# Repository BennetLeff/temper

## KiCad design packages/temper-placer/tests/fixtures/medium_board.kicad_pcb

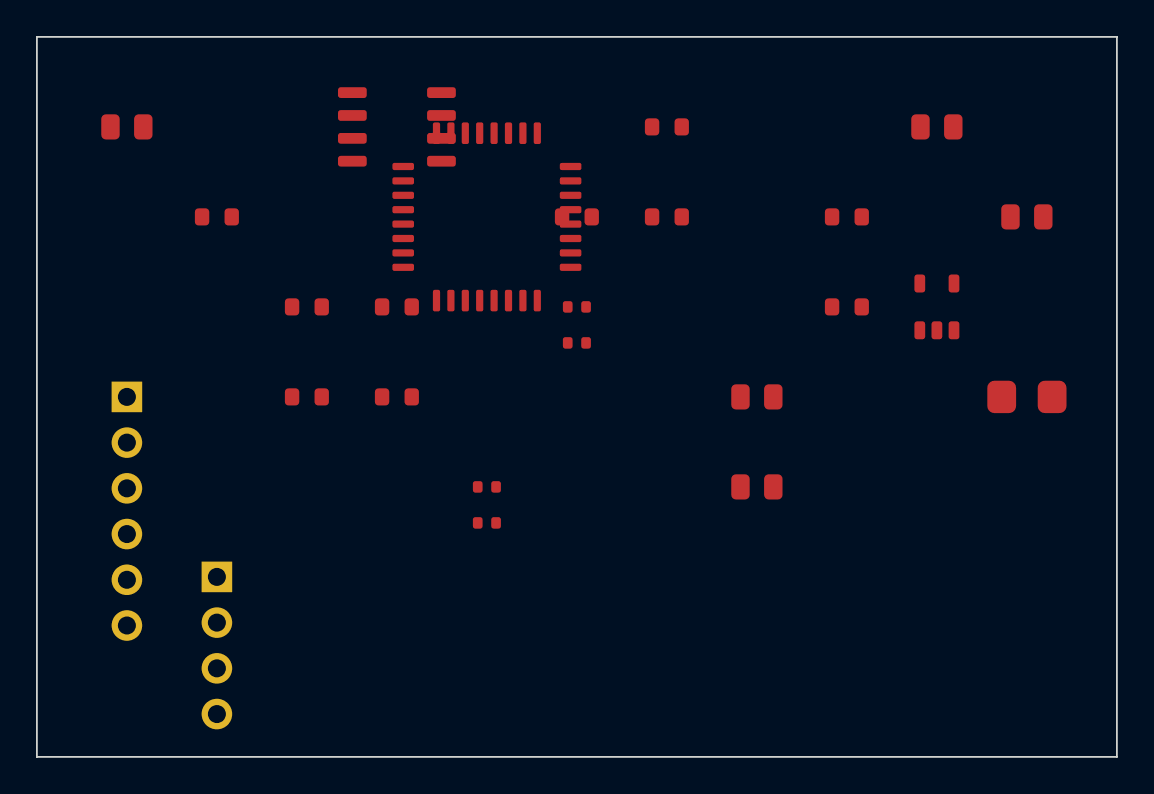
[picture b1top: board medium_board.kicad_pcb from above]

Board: 2 copper layers, 60.0 x 40.0 mm, 25 parts (0 on the bottom side), 18 nets, no tracks yet.

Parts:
C1, C2: 100nF; C_0603_1608Metric
C3: 10nF; C_0603_1608Metric
C4: 1uF; C_0603_1608Metric
C5, C6: 10uF; C_0805_2012Metric
C7, C8: 100pF; C_0402_1005Metric
J1: PROG; PinHeader_1x06_P2.54mm_Vertical
J2: I2C; PinHeader_1x04_P2.54mm_Vertical
L1: 10uH; L_0805_2012Metric
L2: 4.7uH; L_1206_3216Metric
R1, R2: 10k; R_0603_1608Metric
R3, R4: 4.7k; R_0603_1608Metric
R5, R6: 1k; R_0603_1608Metric
R7, R8: 100; R_0805_2012Metric
R9, R10: 100k; R_0402_1005Metric
U1: LM358; SOIC-8_3.9x4.9mm_P1.27mm
U2: AMS1117-3.3; SOT-23-5
U3: ATmega328P; TQFP-32_7x7mm_P0.8mm

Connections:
GND: C1.2, C2.2, C3.2, C4.2, C5.2, C6.2, C7.2, C8.2, J1.2, J2.2, R8.2, U1.4, U2.2, U2.3, U3.6, U3.16, U3.22, U3.27, U3.32
I2C_SCL: J2.4, R2.2, U3.10
I2C_SDA: J2.3, R1.2, U3.9
PWM1: R5.1, U3.17
PWM2: R6.1, U3.18
SIG_A: R1.1, R9.2, U1.1, U3.11, U3.19, U3.28
SIG_B: R2.1, R10.2, U1.2, U3.12, U3.20, U3.29
SIG_C: R5.2, U1.3, U3.13, U3.23, U3.30
SIG_D: R6.2, U1.5, U1.6, U3.14, U3.24, U3.31
SPI_CLK: C7.1, J1.5, U3.3
SPI_CS: C8.1, J1.6, U3.4
SPI_MISO: J1.4, R4.1, U3.2
SPI_MOSI: J1.3, R3.1, U3.1
UART_RX: R10.1, U3.8
UART_TX: R9.1, U3.7
VBAT: C3.1, L1.2, R7.2, U3.25
VCC: C1.1, C4.1, C5.1, L1.1, L2.2, R7.1, U1.7, U1.8, U2.1, U3.26
VCC_3V3: C2.1, C6.1, J1.1, J2.1, L2.1, R3.2, R4.2, R8.1, U2.4, U2.5, U3.5, U3.15, U3.21

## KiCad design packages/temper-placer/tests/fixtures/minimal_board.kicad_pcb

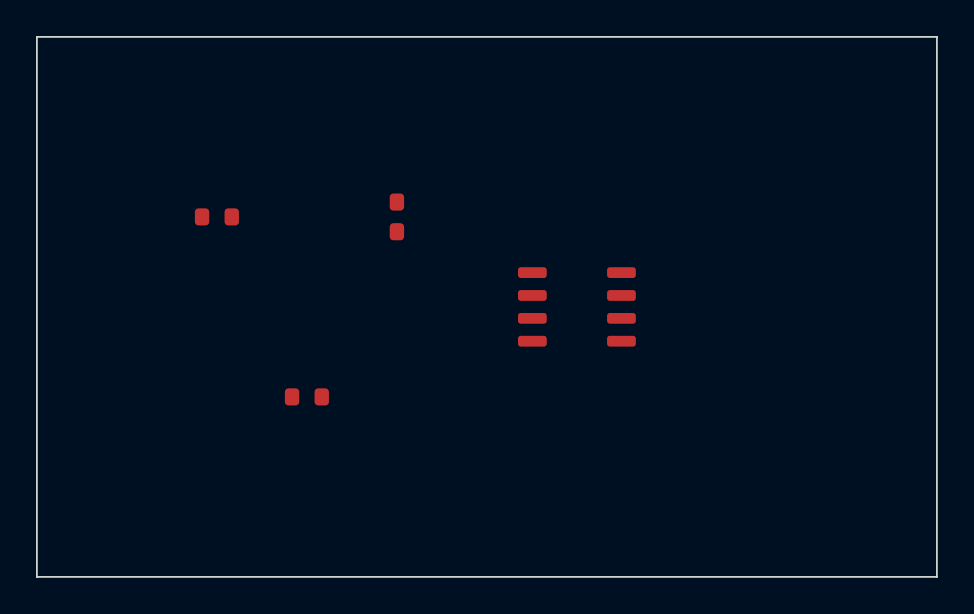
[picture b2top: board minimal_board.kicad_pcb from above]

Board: 2 copper layers, 50.0 x 30.0 mm, 4 parts (0 on the bottom side), 4 nets, no tracks yet.

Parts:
C1: 100nF; C_0603_1608Metric
R1: 10k; R_0603_1608Metric
R2: 4.7k; R_0603_1608Metric
U1: LM358; SOIC-8_3.9x4.9mm_P1.27mm

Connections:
GND: C1.2, R2.1, U1.4
SIG1: R1.1, U1.1, U1.5
SIG2: R1.2, R2.2, U1.2, U1.3, U1.6
VCC: C1.1, U1.7, U1.8

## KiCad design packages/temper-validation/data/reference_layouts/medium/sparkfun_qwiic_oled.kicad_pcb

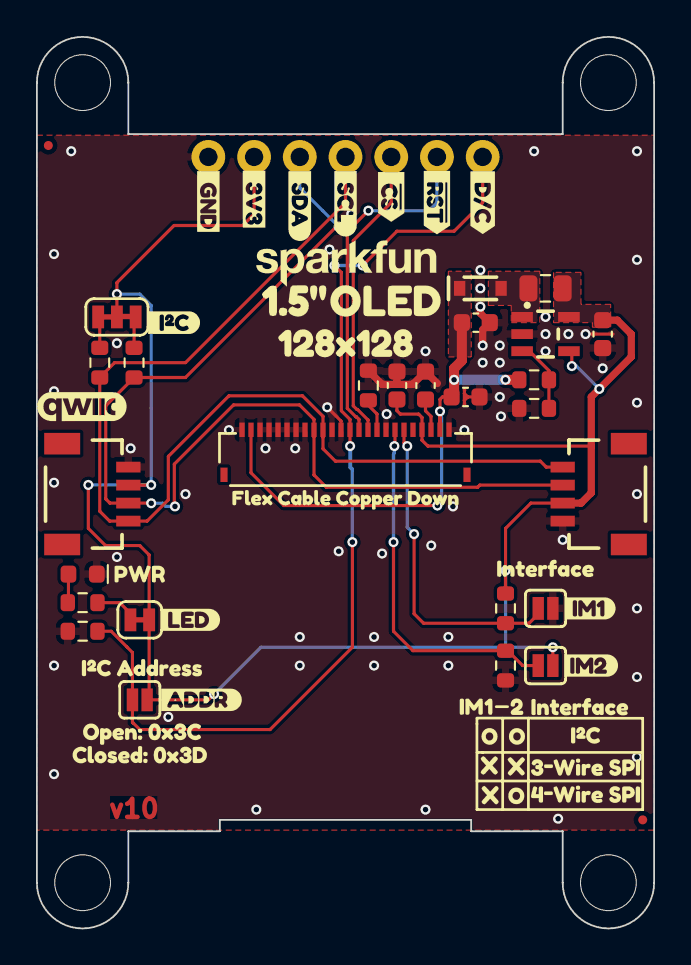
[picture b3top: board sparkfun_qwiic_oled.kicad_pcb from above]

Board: 2 copper layers, 34.3 x 49.5 mm, 70 parts (1 on the bottom side), 18 nets.

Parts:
C1, C2: 1.0uF; C_0603_1608Metric
C3, C4, C5: 4.7uF; C_0603_1608Metric
D1: Red; LED_0603_1608Metric_Red
D2: PMEG4005EJ; SOD-323
FID3, FID4: Fiducial_0.5mm; Fiducial_0.5mm_Mask1mm
G4: OSHW_Logo; Creative_Commons_License
J1, J2: Qwiic_RA; JST_SMD_1.0mm-4_Black
J4: Conn_01x24_FPC; FPC_0.5mm-24
J5: Conn_01x07; 1x07
JP1: LED; Jumper_2_NC_Trace
JP2: I2C; Jumper_3_NC-2_Trace
JP3: ADR; Jumper_2_NO
JP6: IM1; Jumper_2_NO
JP7: IM2; Jumper_2_NO
L1: 10uH; C_0805_2012Metric
R1: 18k; R_0603_1608Metric
R2: 2.1k; R_0603_1608Metric
R3: 4.7k; R_0603_1608Metric
R4, R5: 2.2k; R_0603_1608Metric
R6: 549k; R_0603_1608Metric
R7, R10, R11: 10k; R_0603_1608Metric
ST1, ST2, ST3, ST4: Standoff
TP1: 1.0mm; TestPoint-1.0mm
U2: WEO128128ASAP3N00000; OLED_1.5in_128x128-Folded
U5: AP3012; SOT23-5
kibuzzard-65A8A8B4: G***; kibuzzard-65A8A8B4
kibuzzard-67BF7EBF: G***; kibuzzard-67BF7EBF
kibuzzard-67BF7ED9: G***; kibuzzard-67BF7ED9
kibuzzard-67BF7F2F: G***; kibuzzard-67BF7F2F
kibuzzard-67BF7F13: G***; kibuzzard-67BF7F13
kibuzzard-680E7A4B: G***; kibuzzard-680E7A4B
kibuzzard-680E7A69: G***; kibuzzard-680E7A69
kibuzzard-680FC73E: G***; kibuzzard-680FC73E
kibuzzard-680FC89E: G***; kibuzzard-680FC89E
kibuzzard-680FC883: G***; kibuzzard-680FC883
kibuzzard-680FC897: G***; kibuzzard-680FC897
kibuzzard-680FC957: G***; kibuzzard-680FC957
kibuzzard-680FCA9D: G***; kibuzzard-680FCA9D
kibuzzard-680FCA96: G***; kibuzzard-680FCA96
kibuzzard-680FCADD: G***; kibuzzard-680FCADD
kibuzzard-680FCAEB: G***; kibuzzard-680FCAEB
kibuzzard-684C656A: G***; kibuzzard-684C656A
kibuzzard-685B1775: G***; kibuzzard-685B1775
kibuzzard-6893A61C, kibuzzard-6893A61C#2, kibuzzard-6893A61C#3: G***; kibuzzard-6893A61C
kibuzzard-689381EF, kibuzzard-689381EF#2, kibuzzard-689381EF#3: G***; kibuzzard-689381EF
kibuzzard-6851867B: G***; kibuzzard-6851867B
kibuzzard-6851871B: G***; kibuzzard-6851871B
kibuzzard-6893822D: G***; kibuzzard-6893822D
kibuzzard-6893824B: G***; kibuzzard-6893824B
kibuzzard-68518672: G***; kibuzzard-68518672
kibuzzard-68938236: G***; kibuzzard-68938236
kibuzzard-68938244: G***; kibuzzard-68938244
kibuzzard-68938257: G***; kibuzzard-68938257
kibuzzard-68938266: G***; kibuzzard-68938266
kibuzzard-68938270: G***; kibuzzard-68938270

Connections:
3.3V: C1.1, C4.1, J1.2, J2.2, J4.21, J5.2, JP1.2 (B), JP2.2 (B), JP3.2 (B), JP7.2 (B), L1.1, R10.1, U5.4 (~SHDN), U5.5 (IN)
12V: C2.1, C5.1, D2.1 (K), J4.2, J4.23, R1.2, TP1.1
/12V_OUT: D2.2 (A), L1.2, U5.1 (SW)
D/C: J4.13, J5.7, JP3.1 (A), R7.2
GND: C1.2, C2.2, C3.2, C4.2, C5.2, D1.1 (K), J1.1, J2.1, J4.1, J4.3, J4.4, J4.5, J4.6, J4.7, J4.8, J4.11, J4.12, J4.17, J4.24, J5.1, JP6.1 (A), R2.1, R6.1, R7.1, R11.2, U5.2 (GND)
unnamed: D1.2 (A), R3.1
unnamed: J4.16, R6.2
unnamed: J4.18, JP7.1 (A), R11.1
unnamed: J4.19, JP6.2 (B), R10.2
unnamed: C3.1, J4.22
unnamed: JP1.1 (A), R3.2
unnamed: JP2.1 (A), R5.1
unnamed: JP2.3 (C), R4.2
unnamed: R1.1, R2.2, U5.3 (FB)
SCL/SCK: J1.4, J2.4, J4.10, J5.4, R5.2
SDA/SDI: J1.3, J2.3, J4.9, J5.3, R4.1
~CS: J4.15, J5.5
~RST: J4.14, J5.6

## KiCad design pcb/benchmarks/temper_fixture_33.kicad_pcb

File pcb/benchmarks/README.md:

# Benchmark Fixtures (quarantined)

Boards in this directory are **synthetic benchmark fixtures**, not the
production design. They exist only to exercise the placer/router algorithms.

## Rules

- A board here can **never** be a production pipeline input. The artifact
  identity gate (plan `docs/plans/2026-07-15-001-feat-artifact-identity-provenance-plan.md`,
  unit U3/U4) infers role from this path: `pcb/benchmarks/**` ⇒ fixture.
- Nothing here is derived from `elec/src/*.ato`. Do not treat it as the design.

## Current contents

- `temper_fixture_33.kicad_pcb` — 33-component synthetic fixture. The real
  Temper design has ~100 components (`elec/build/default.net`).

## Sunset

This directory is temporary. Once the production board is generated from
schematics and the placer/router are re-benchmarked against it (plan
`2026-07-15-001` unit U6), this fixture is deleted and the committed
`.kicad_pcb` inventory becomes exactly one board.

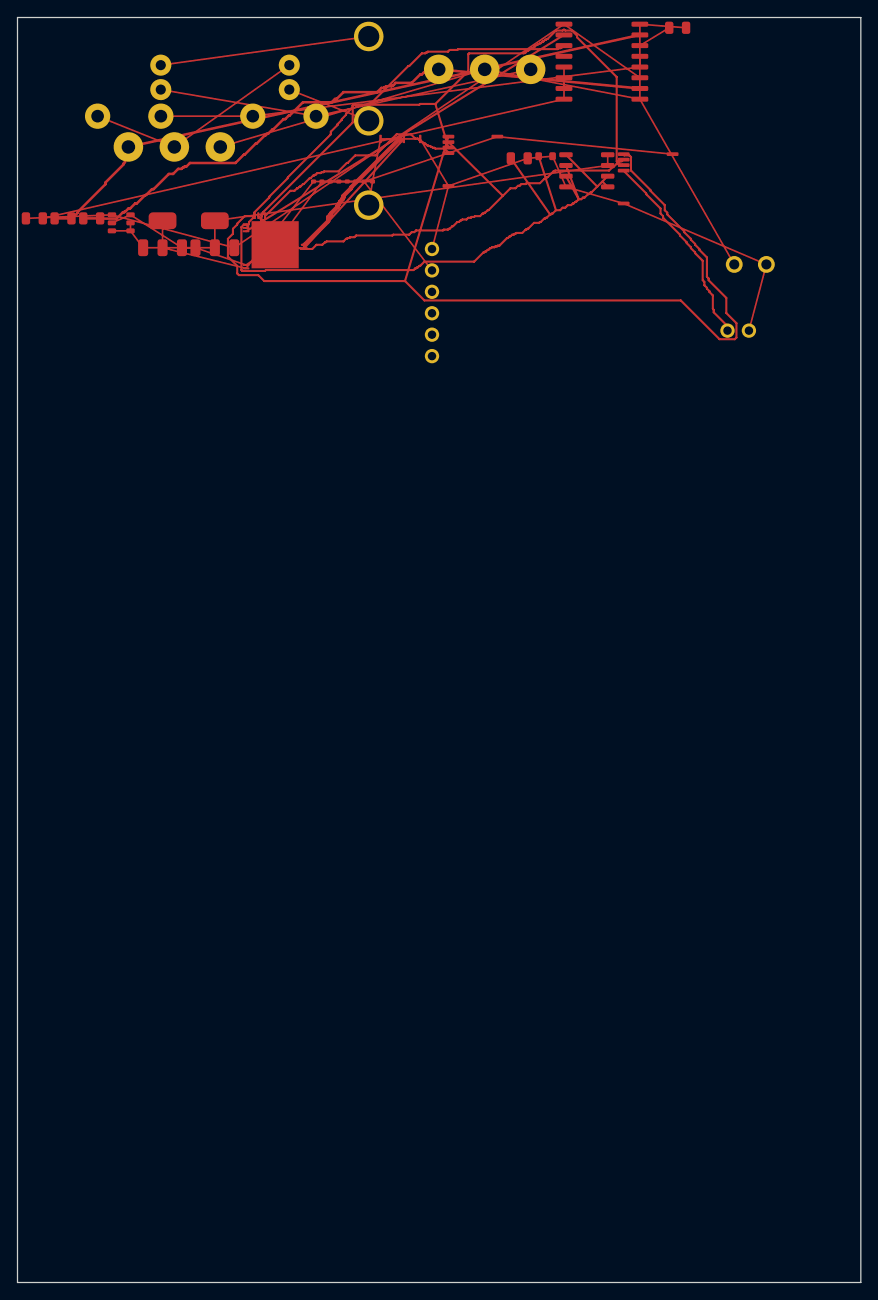
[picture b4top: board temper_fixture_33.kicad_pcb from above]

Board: 4 copper layers, 100.0 x 150.0 mm, 33 parts (0 on the bottom side), 24 nets.

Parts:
C_BOOT: 10uF; C_0805_2012Metric
C_BUS1, C_BUS2: 330uF/400V; CP_Radial_D18.0mm_P7.50mm
C_CT_FILT: 100pF; C_0603_1608Metric
C_MCU_1, C_MCU_2, C_MCU_3: 100nF; C_0402_1005Metric
C_MCU_4: 10uF; C_0402_1005Metric
C_VCC: 10uF; C_0805_2012Metric
D1, D2: 1N5408; D_DO-201AD_P15.24mm_Horizontal
J_AC_IN: IEC_C14; IEC_C14_Male
J_COIL: Coil; PhoenixContact_MCV_1,5_2-G-3.81_1x02_P3.81mm_Vertical
J_DEBUG: Debug; PinHeader_1x06_P2.54mm_Vertical
J_NTC: NTC; PinHeader_1x02_P2.54mm_Vertical
J_USB: USB_C; USB_C_Receptacle_HRO_TYPE-C-31-M-12
MAX31865: MAX31865; TSSOP-20_4.4x6.5mm_P0.65mm
MH1, MH2, MH3, MH4: MountingHole_3.2mm_M3
Q1, Q2: IKW40N120H3; TO-247-3_Horizontal_TabDown
R_BURDEN: 33R; R_0805_2012Metric
R_GATE_H: 4.7R; R_0805_2012Metric
R_GATE_L: 4.7R; R_0805_2012Metric
U_BUCK: LMR51430; SOT-23-6
U_CT: MAX31865; TSSOP-20_4.4x6.5mm_P0.65mm
U_GATE: UCC21550; SOIC-16W_7.5x10.3mm_P1.27mm
U_LDO_3V3: AMS1117-3.3; SOT-223-3_TabPin2
U_LDO_5V: AMS1117-5.0; SOT-223-3_TabPin2
U_MCU: ESP32-S3-WROOM-1; QFN-56-1EP_7x7mm_P0.4mm_EP5.6x5.6mm
U_OPAMP_CT: LM358; SOIC-8_3.9x4.9mm_P1.27mm

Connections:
+3V3: C_MCU_1.1, C_MCU_2.1, C_MCU_3.1, C_MCU_4.1, J_DEBUG.2, MAX31865.20, U_CT.20, U_LDO_3V3.2, U_LDO_3V3.4, U_MCU.1
+5V: U_BUCK.2, U_BUCK.4, U_LDO_3V3.3, U_LDO_5V.2, U_LDO_5V.4, U_OPAMP_CT.7, U_OPAMP_CT.8
+15V: C_VCC.1, U_BUCK.3, U_GATE.1, U_GATE.11, U_LDO_5V.3
AC_L: D1.1, J_AC_IN.1
AC_N: D2.2, J_AC_IN.2
CGND: C_VCC.2, U_GATE.5, U_GATE.6, U_GATE.7, U_GATE.8
DC_BUS+: C_BUS1.1, D1.2, Q1.2
DC_BUS-: C_BUS2.2, D2.1, Q2.3
GATE_H: Q1.1, R_GATE_H.1, R_GATE_H.2, U_GATE.15
GATE_L: Q2.1, R_GATE_L.1, R_GATE_L.2, U_GATE.10
GND: C_CT_FILT.2, C_MCU_1.2, C_MCU_2.2, C_MCU_3.2, C_MCU_4.2, J_AC_IN.3, J_COIL.2, J_DEBUG.1, J_NTC.2, J_USB.A1, J_USB.A12, MAX31865.10, R_BURDEN.2, U_BUCK.1, U_BUCK.5, U_BUCK.6, U_CT.10, U_LDO_3V3.1, U_LDO_5V.1, U_MCU.2, U_MCU.57, U_OPAMP_CT.4
I_SENSE: C_CT_FILT.1, R_BURDEN.1, U_MCU.15, U_OPAMP_CT.1, U_OPAMP_CT.2, U_OPAMP_CT.3, U_OPAMP_CT.5, U_OPAMP_CT.6
PGND: C_BUS1.2, C_BUS2.1, U_GATE.12, U_GATE.13
PWM_H: U_GATE.2, U_MCU.13
PWM_L: U_GATE.3, U_MCU.14
SPI_CLK: MAX31865.1, U_CT.1, U_MCU.20
SPI_CS_TEMP: U_CT.4, U_MCU.23
SPI_MISO: MAX31865.3, U_CT.3, U_MCU.22
SPI_MOSI: MAX31865.2, U_CT.2, U_MCU.21
SW_NODE: C_BOOT.2, J_COIL.1, Q1.3, Q2.2, U_GATE.9, U_GATE.16
TEMP_SENSE: J_NTC.1, MAX31865.4
USB_D+: J_USB.A6, U_MCU.40
USB_D-: J_USB.B6, U_MCU.41
VCC_BOOT: C_BOOT.1, U_GATE.14

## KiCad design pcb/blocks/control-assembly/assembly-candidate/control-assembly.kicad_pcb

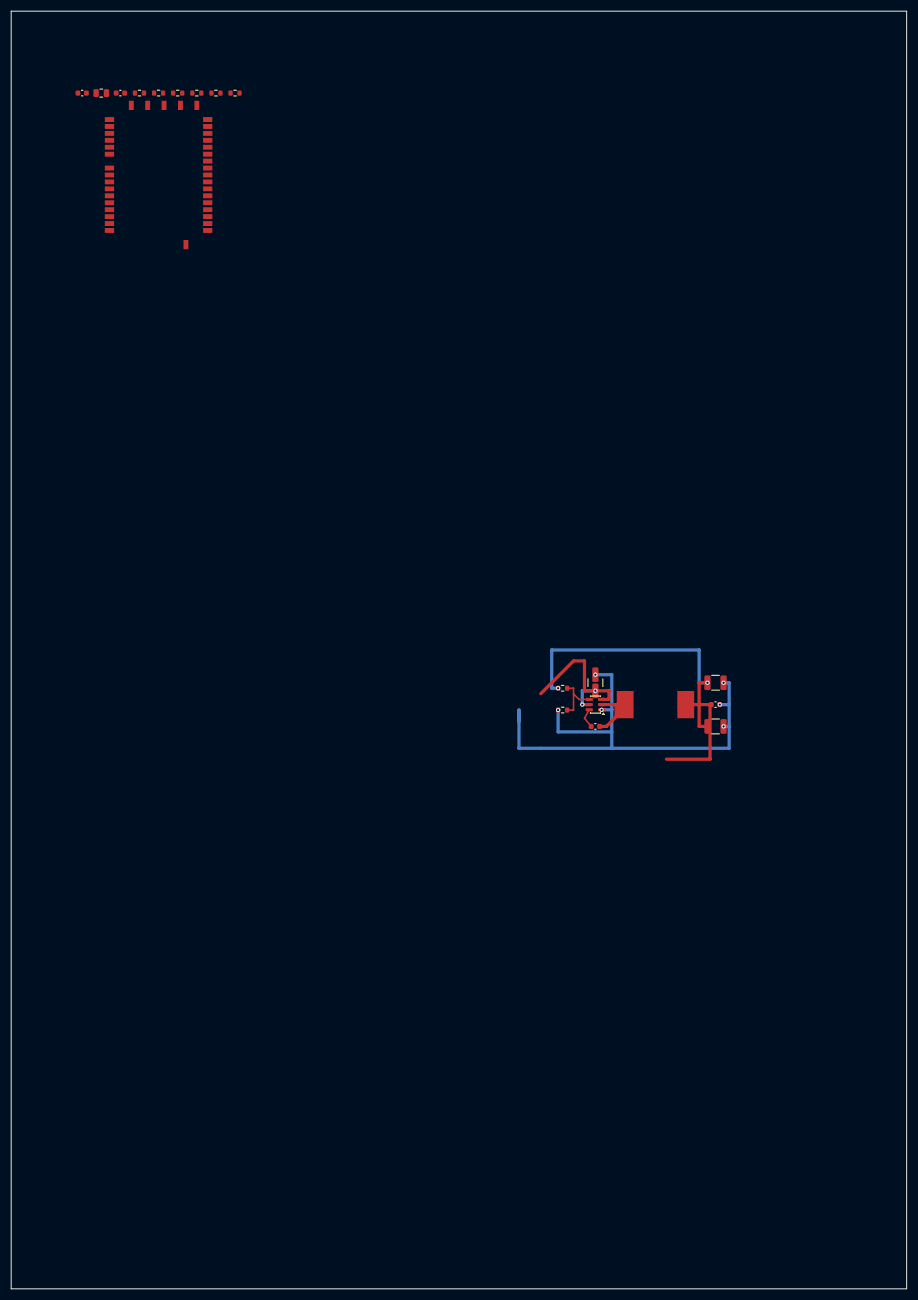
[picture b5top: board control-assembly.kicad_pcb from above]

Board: 6 copper layers, 164.0 x 234.0 mm, 19 parts (0 on the bottom side), 10 nets.

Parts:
C1, C3, C4: ?; C_1210_3225Metric
C2, C5, C6, C8: ?; C_0603_1608Metric
C7: ?; C_0805_2012Metric
L1: ?; L_Bourns_SRP1265A
R1, R2, R3, R4, R5, R6: ?; R_0603_1608Metric
SW1, SW2: ?; R_0603_1608Metric
U1: ?; SOT-23-6
U2: ?; ESP32-S3-WROOM-1

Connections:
boot: C2.1, U1.6
buck-vcc: C1.1, U1.3, U1.5
buck-vcc-1: C3.1, C4.1, C5.1, C6.1, C7.1, L1.2, R1.1, R3.1, R4.1, R5.1, R6.1, U2.2
en: C8.1, R3.2, SW1.1, U2.3
fb: R1.2, R2.1, U1.4
gnd: C1.2, C3.2, C4.2, C5.2, C6.2, C7.2, C8.2, R2.2, SW1.2, SW2.2, U1.1, U2.1
io0: R4.2, SW2.1, U2.27
scl: R6.2, U2.32
sda: R5.2, U2.31
sw: C2.2, L1.1, U1.2

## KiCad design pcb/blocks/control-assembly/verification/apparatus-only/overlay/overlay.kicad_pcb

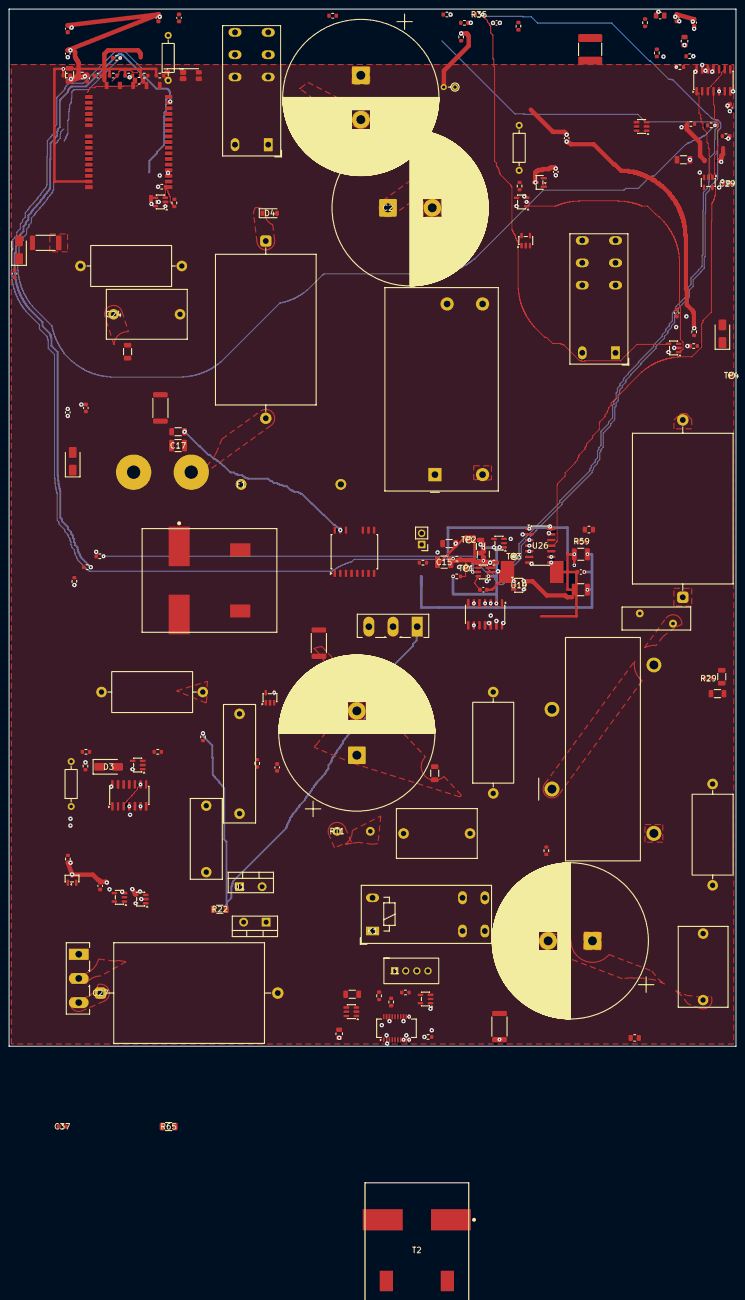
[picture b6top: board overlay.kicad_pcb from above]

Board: 6 copper layers, 164.0 x 234.0 mm, 168 parts (0 on the bottom side), 98 nets.

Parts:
C1: ?; C_Rect_L18.0mm_W7.0mm_P15.00mm_FKS3_FKP3
C2, C3, C4, C5: ?; CP_Radial_D35.0mm_P10.00mm_SnapIn
C6: ?; C_Rect_L26.5mm_W7.0mm_P22.50mm_MKS4
C7, C8, C24: ?; C_Rect_L18.0mm_W11.0mm_P15.00mm_FKS3_FKP3
C9: CL32B106KBJZW6E; C_1210_3225Metric
C10, C13, C39: C0603C104K5RACTU; C_0603_1608Metric
C11, C12: CL32B226KAJNNWE; C_1210_3225Metric
C14: ?; C_2220_5750Metric
C15, C17: ?; C_1210_3225Metric
C16, C18, C19, C20, C21, C22, C23, C28, C29, C30, C31, C32, C33, C34, C35, C36, C37, C38: ?; C_0603_1608Metric
C25, C26, C27: ?; C_Axial_L34.0mm_D22.5mm_P40.00mm_Horizontal
C40: GRM21BR71A106KE51L; C_0805_2012Metric
C41: GRM188R71A105KA61D; C_0603_1608Metric
D1, D2, D3: ?; D_SMA
D4: ?; D_SOD-123
F1: ?; Fuse_Holder_5x20mm
J1: ?; JST_XH_B4B-XH-A_1x04_P2.50mm_Vertical
J2: ?; PinHeader_1x02_P2.54mm_Vertical
K1: ?; Relay_SPST_Schrack-RT33K012
K2, K3: ?; Relay_SPDT_Schrack-RT314012
L1: ?; CMC_B82726S
L2: SRP1265A-5R6M; L_Bourns_SRP1265A
PS1: ?; Converter_ACDC_MeanWell_IRM-10-xx_THT
Q1, Q2: ?; SOT-23
R1, R60, R75: ?; R_Axial_DIN0207_L6.3mm_D2.5mm_P10.16mm_Horizontal
R2, R3, R12, R13, R28, R40: ?; R_0805_2012Metric
R4, R5, R14, R15: ?; R_2512_6332Metric
R6, R7, R8, R9: ?; R_Axial_DIN0918_L18.0mm_D9.0mm_P22.86mm_Horizontal
R10, R11, R18, R22, R25, R46, R47, R48, R51, R52, R53, R65: ?; R_1206_3216Metric
R16: RC0603FR-07100KL; R_0603_1608Metric
R17: RC0603FR-0722K1L; R_0603_1608Metric
R19, R20, R21, R23, R24, R26, R27, R29, R31, R32, R33, R35, R36, R37, R38, R39, R41, R42, R43, R44, R45, R49, R50, R54, R56, R57, R58, R59, R61, R62, R63, R64, R66, R67, R68, R69, R70: ?; R_0603_1608Metric
R30: ?; LitzPad_15A
R34: ?; L_0603_1608Metric
R55: ?; R_Axial_DIN0204_L3.6mm_D1.6mm_P2.54mm_Vertical
R71, R72: RC0603FR-0710KL; R_0603_1608Metric
R73, R74: RC0603FR-074K7L; R_0603_1608Metric
RT1: ?; R_Disc_D15.0mm_W7.0mm_P7.5mm
RV1: ?; RV_Disc_D15.5mm_W5.2mm_P7.5mm
SW1, SW2: EVQ-P7A01P; SW_SPST_EVQP7A
T1, T2: ?; CST3015
TP1, TP2, TP3, TP4: ?; TestPoint_Pad_D1.0mm
U1, U2: ?; TO-220-2_Vertical
U3: LMR51430XDDCR; SOT-23-6
U4, U5: ?; TO-247-3_Vertical
U6: ?; SOIC16W_Isolated
U7: ?; D_SMA
U8: ?; SSOP-20_3.9x8.7mm_P0.635mm
U9, U10, U11, U12, U14, U15, U16, U17, U18, U19, U20, U22: ?; SOT-23-5
U13, U21: ?; SOT-23-6
U23, U24, U25, U26: ?; SOIC-14_3.9x8.7mm_P1.27mm
U27: ESP32-S3-WROOM-1-N8R8; ESP32-S3-WROOM-1

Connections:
+3V3: C11.1, C12.1, C13.1, C20.1, C21.1, C30.1, C34.1, C38.1, C39.1, C40.1, L2.2, R16.1, R26.1, R34.1, R42.1, R43.1, R44.1, R56.1, R57.1, R61.1, R62.1, R66.1, R69.1, R70.1, R71.1, R72.1, R73.1, R74.1, U6.3, U6.8, U9.3, U9.4, U13.5, U15.5, U16.5, U17.5, U18.5, U19.5, U20.3, U20.5, U21.5, U22.2, U22.5, U23.14, U24.14, U25.14, U26.2, U26.13, U26.14, U27.2
+15V: C9.1, C15.1, C16.1, PS1.3, R1.1, R10.1, R11.1, R75.1, U3.3, U3.5
+15V_LS: C23.1, U6.11, U7.2
+170V_BUS: C2.1, C4.1, C14.1, C24.1, PS1.1, R4.1, R6.1, R46.1, R51.1, U1.1, U4.2
DC_BUS_RTN: C3.2, C5.2, C8.2, K3.1, R5.2, T2.2, U2.2
GATE_HS: R18.1, U6.15
GATE_LS: R22.2, R23.1, U5.1
I_SENSE: C28.1, R25.1, R26.2, R27.1, T1.3, U15.3
OCP2_VREF_2V5: U9.5, U16.4, U19.4
PWR_RTN: C2.2, C3.1, C4.2, C5.1, C6.1, C7.2, C14.2, K2.1, L1.3, PS1.2, R4.2, R5.1, R8.1, T1.2
RTD_HW_FAULT: R43.2, U14.4, U24.2
SHUTDOWN: TP1.1, TP2.1, U6.5, U26.6, U26.10
SW_NODE: C25.1, C26.1, C27.1, D4.1, R19.2, U4.3, U5.2
V_BUS_SENSE: C36.1, R53.2, R54.1
WDT_RESET_N: U20.2, U26.12
ac_n: C1.2, L1.2, RV1.2
bias: R28.1, U8.4, U8.5
boot: C10.1, U3.6
cs_n: R32.2, U8.16
discharge.k_dis1-coil1: D2.1, K2.2, R10.2
discharge.k_dis1-coil2: D2.2, D3.2, K2.5, K3.5, Q2.1
discharge.k_dis1-nc: K2.4, R7.2, R14.1
discharge.k_dis2-coil1: D3.1, K3.2, R11.2
discharge.k_dis2-nc: K3.4, R9.2, R15.1
discharge.q_dis_drv-g: Q2.2, R12.2, R13.1
discharge.r_dis1a-p2: R6.2, R7.1
discharge.r_dis2a-p2: R8.2, R9.1
discharge.r_snub1-p2: C7.1, R14.2
discharge.r_snub2-p2: C8.1, R15.2
en: C41.1, R71.2, SW1.1, U27.3
fb: R16.2, R17.1, U3.4
gnd: C6.2, C9.2, C11.2, C12.2, C13.2, C15.2, C16.2, C18.2, C19.2, C20.2, C21.2, C28.2, C29.2, C30.2, C31.2, C32.2, C33.2, C34.2, C35.2, C36.2, C37.2, C38.2, C39.2, C40.2, C41.2, J2.2, PS1.4, Q1.3, Q2.3, R3.2, R13.2, R17.2, R24.2, R25.2, R27.2, R36.2, R38.2, R39.2, R41.2, R45.2, R49.2, R54.2, R55.2, R58.2, R60.2, R63.2, R65.2, R67.2, SW1.2, SW2.2, T1.4, T2.4, U3.1, U6.4, U8.9, U8.13, U8.18, U8.19, U9.2, U10.2, U11.2, U12.3, U13.2, U13.4, U14.3, U15.2, U16.2, U17.2, U18.2, U19.2, U20.1, U21.2, U21.4, U22.3, U23.7, U23.11, U23.12, U23.13, U24.5, U24.7, U24.11, U24.12, U24.13, U25.5, U25.7, U25.8, U25.11, U25.12, U25.13, U26.7, U27.1
hb-gnd: C23.2, C24.2, R23.2, T2.1, U5.3, U6.9
hb.gate_hs.driver-p1: R24.1, U6.6
hb.gate_hs.driver-p1-1: C17.1, C22.1, U6.16, U7.1
hb.gate_hs.driver-p2: C17.2, C22.2, D4.2, U6.14
hb.power_loop.q_high-g: R18.2, R19.1, U4.1
ina: C18.1, R20.2, U6.1
inb: C19.1, R21.2, U6.2
input: R22.1, U6.10
io0: R72.2, SW2.1, U27.27
power_in.bypass_relay-coil1: D1.1, K1.1, R1.2
power_in.bypass_relay-coil2: D1.2, K1.2, Q1.1
power_in.ntc-no: K1.3, RT1.2, U1.2, U2.1
power_in.q_relay_drv-g: Q1.2, R2.2, R3.1
refin_n: R28.2, U8.6, U8.7, U10.3, U11.4
rtd_force_n: J1.4, U8.12
rtd_force_p: J1.1, U8.8
rtd_pan.high_window-out: U11.1, U12.2
rtd_pan.low_window-out: U10.1, U12.1
rtd_pan.r_high_top-inp: R37.2, R38.1, U11.3
rtd_pan.r_low_top-inn: R35.2, R36.1, U10.4
rtd_pan.rail_monitor-ina_p: R40.2, R41.1, U13.3
rtd_pan.rail_monitor-outa: R42.2, U13.1, U14.2
rtd_sense_n: J1.3, U8.11
rtd_sense_p: J1.2, U8.10
s1: C37.1, R65.1, T2.3, U19.3
safety-line: R55.1, R56.2, U17.4
safety-line-1: R60.1, R61.2, U18.4
safety.coil_thermal-line: R64.2, U18.1, U24.8
safety.coil_thermal.comp-inp: R62.2, R63.1, R64.1, U18.3
safety.fault_any_or-a2: U24.3, U24.9, U25.3
safety.fault_any_or-y2: U24.6, U26.9
safety.fault_or3-b2: U25.4, U25.9
safety.fault_or3-y2: U25.6, U26.1
safety.fault_or-a2: U23.3, U23.9
safety.fault_or-b2: U23.4, U26.11
safety.fault_or-y2: U23.6, U24.1
safety.latch-b2: U26.5, U26.8
safety.ocp2-line: TP3.1, U19.1, U25.2
safety.ocp-line: U15.1, U23.1
safety.ocp.comp-inn: R44.2, R45.1, U15.4
safety.ovp-line: R50.2, U16.1, U23.2
safety.ovp.comp-inp: R48.2, R49.1, R50.1, U16.3
safety.ovp.r_adc_top1-p2: R51.2, R52.1
safety.ovp.r_adc_top2-p2: R52.2, R53.1
safety.ovp.r_div_top1-p2: R46.2, R47.1
safety.ovp.r_div_top2-p2: R47.2, R48.1
safety.thermal-line: R59.2, U17.1, U23.8
safety.thermal.comp-inp: R57.2, R58.1, R59.1, U17.3
safety.uvlo_logic-line: R70.2, TP4.1, U22.4, U25.1
safety.uvlo_logic.mon-ina_p: R66.2, R67.1, R68.1, U21.3
safety.uvlo_logic.mon-outa: R68.2, R69.2, U21.1, U22.1
scl: R74.2, U27.32
sclk: R29.2, U8.15, U27.12
sda: R73.2, U27.31
sdi: R31.2, U8.14
sdo: R33.1, U8.17
sw: C10.2, L2.1, U3.2
tank-out: R30.2, T1.1
tank.c_tank1-p2: C25.2, C26.2, C27.2, R30.1
thermal.j_fan-p1: J2.1, R75.2
vbias: R35.1, R37.1, U9.1
vcc: C29.1, C31.1, C32.1, C33.1, C35.1, R34.2, R40.1, U8.2, U8.3, U10.5, U11.5, U12.5, U14.5
w1_1: C1.1, F1.2, L1.1, RV1.1
w1_2: K1.4, L1.4, RT1.1
y: R39.1, U12.4, U14.1
y1: U26.3, U26.4

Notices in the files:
parts and their libraries:
https://creativecommons.org/licenses/by-sa/4.0
Released under the Creative Commons Attribution Share-Alike 4.0 License
